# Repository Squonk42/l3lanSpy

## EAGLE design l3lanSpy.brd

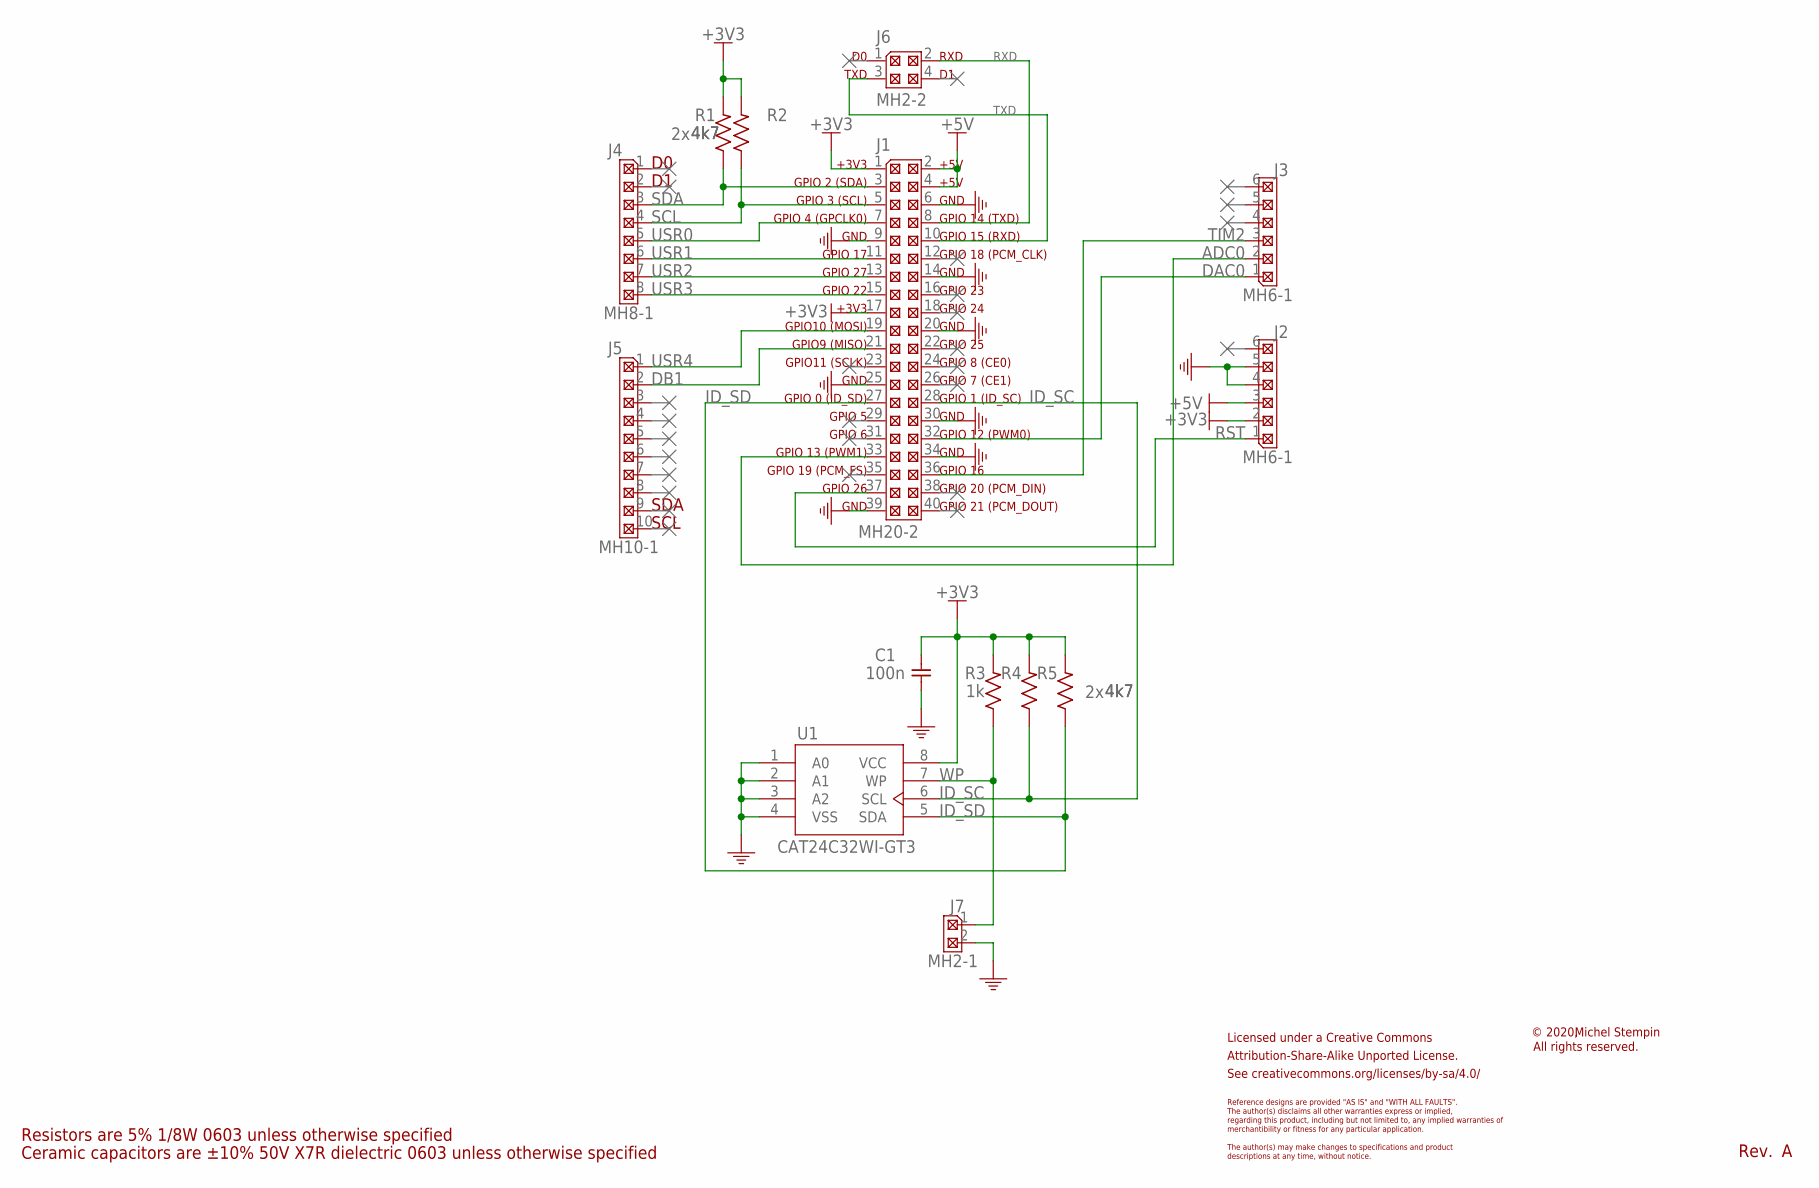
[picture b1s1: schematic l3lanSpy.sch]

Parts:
C1: 100n; C0603
J1: MH20-2; MH20-2-0.1
J2, J3: MH6-1; MH6-1-0.1
J4: MH8-1; MH8-1-0.1
J5: MH10-1; MH10-1-0.1
J6: MH2-2; MH2-2-0.1
J7: MH2-1; MH2-1-0.1
LOGO1: CC-BY-SA_LOGO
R1, R2, R4, R5: 4k7; R0603
R3: 1k; R0603
U1: CAT24C32WI-GT3; SOIC-8

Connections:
+3V3: C1.1, J1.1, J1.17, J2.2, R1.2, R2.2, R3.2, R4.2, R5.2, U1.8 (VCC)
+5V: J1.2, J1.4, J2.3
ADC0: J1.33, J3.2
DAC0: J1.32, J3.1
DB1: J1.21, J5.2
GND: C1.2, J1.6, J1.9, J1.14, J1.20, J1.25, J1.30, J1.34, J1.39, J2.4, J2.5, J7.2, U1.1 (A0), U1.2 (A1), U1.3 (A2), U1.4 (VSS)
ID_SC: J1.28, R4.1, U1.6 (SCL)
ID_SD: J1.27, R5.1, U1.5 (SDA)
RST: J1.37, J2.1
RXD: J1.8, J6.2
SCL: J1.5, J4.4, R2.1
SDA: J1.3, J4.3, R1.1
TIM2: J1.36, J3.3
TXD: J1.10, J6.3
USR0: J1.7, J4.5
USR1: J1.11, J4.6
USR2: J1.13, J4.7
USR3: J1.15, J4.8
USR4: J1.19, J5.1
WP: J7.1, R3.1, U1.7 (WP)

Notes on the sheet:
+3V3
GPIO 2 (SDA)
GPIO 3 (SCL)
GPIO 4 (GPCLK0)
GND
GPIO 17
GPIO 27
GPIO 22
GPIO10 (MOSI)
GPIO9 (MISO)
GPIO11 (SCLK)
GPIO 0 (ID_SD)
GPIO 5
GPIO 6
GPIO 13 (PWM1)
GPIO 19 (PCM_FS)
GPIO 26
+5V
GPIO 14 (TXD)
GPIO 15 (RXD)
GPIO 18 (PCM_CLK)
GPIO 23
GPIO 24
GPIO 25
GPIO 8 (CE0)
GPIO 7 (CE1)
GPIO 1 (ID_SC)
GPIO 12 (PWM0)
GPIO 16
GPIO 20 (PCM_DIN)
GPIO 21 (PCM_DOUT)
SDA
SCL
RXD
TXD
Rev.
Licensed under a Creative Commons
Attribution-Share-Alike Unported License.
See creativecommons.org/licenses/by-sa/4.0/
Reference designs are provided "AS IS" and "WITH ALL FAULTS".

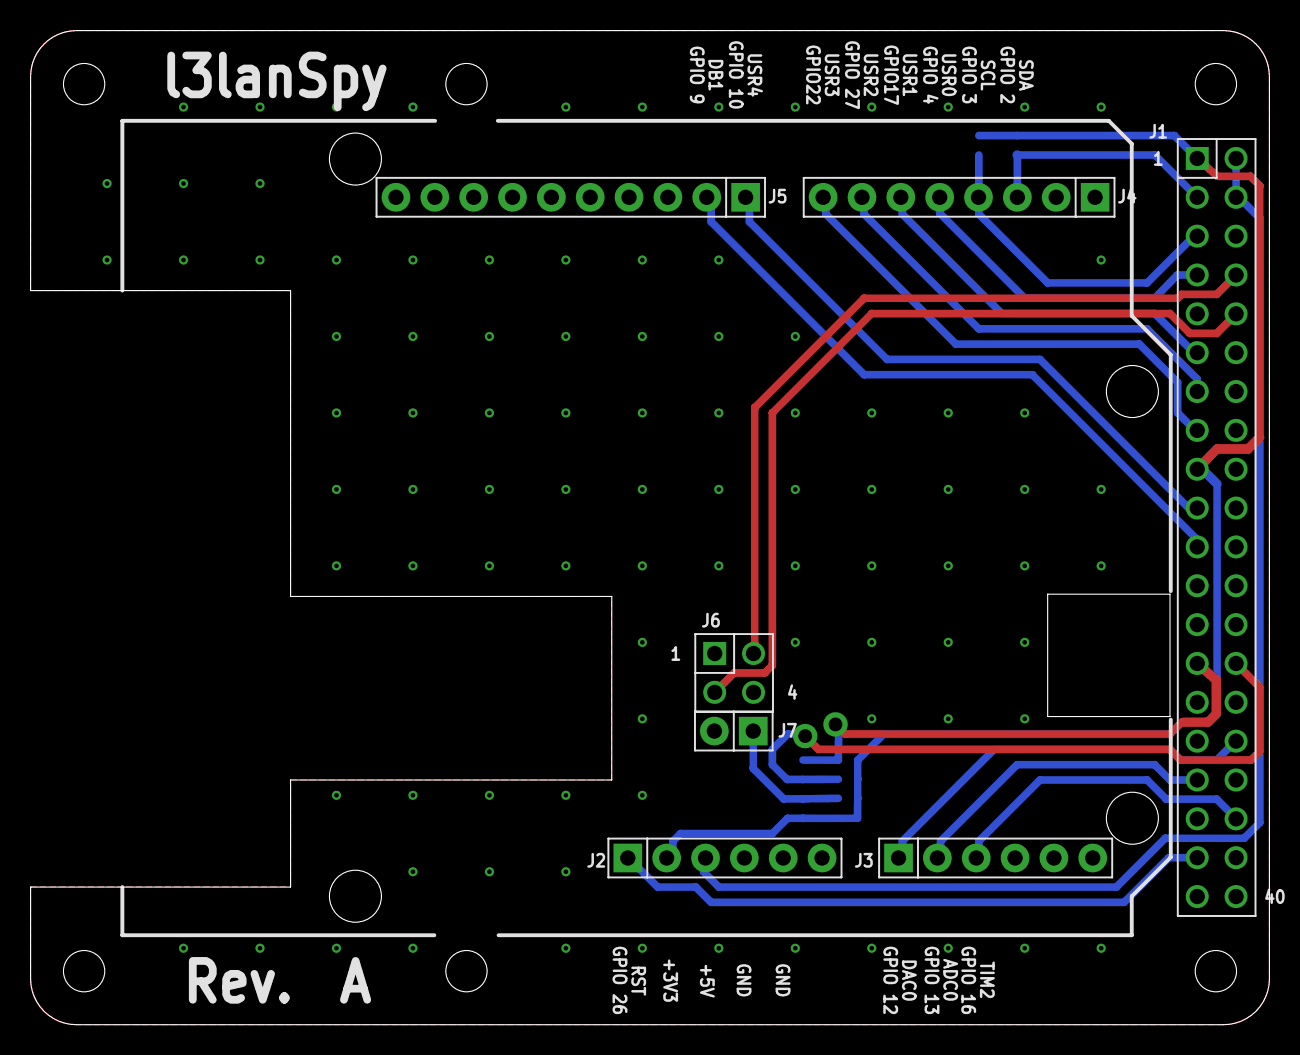
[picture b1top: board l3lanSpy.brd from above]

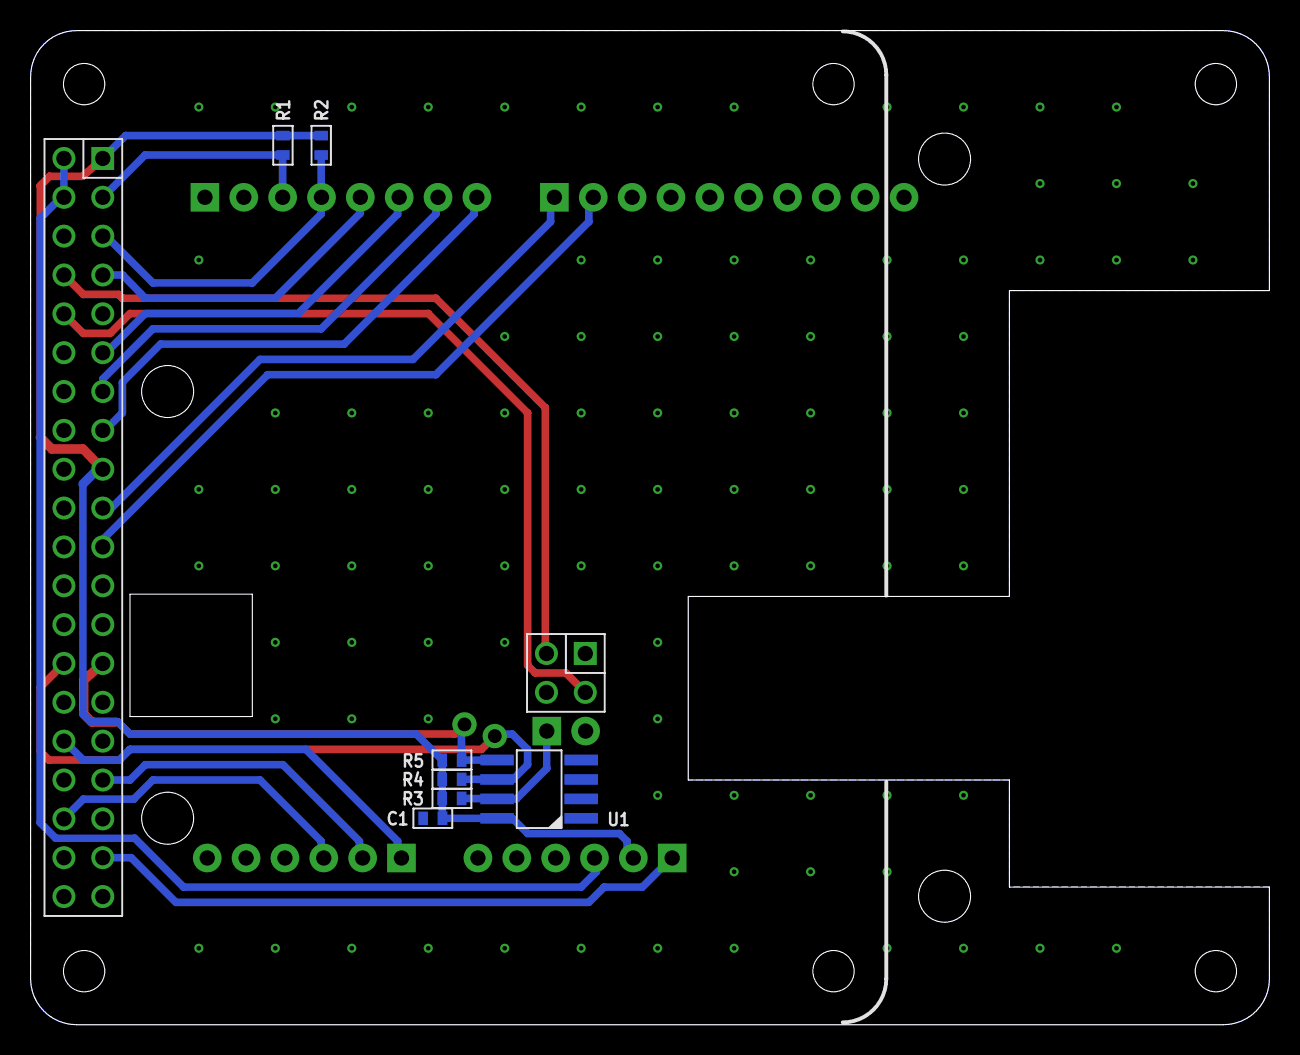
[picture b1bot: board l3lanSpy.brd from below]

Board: 2 copper layers, 81.0 x 65.0 mm, 19 parts (7 on the bottom side), 20 nets.

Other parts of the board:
DRILEGEND: DRILEGEND
U$1: TD1208_EVB
U$2: RASPBERRY_PI_3A+
U$3: A5L-LOC

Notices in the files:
KiCAD/l3lanSpy.sch:
All rights reserved.
© 2020,
parts and their libraries:
l3lanSpy: See creativecommons.org/licenses/by-sa/4.0/ for details.
l3lanSpy: See creativecommons.org/licenses/by-sa/3.0/ for details.
